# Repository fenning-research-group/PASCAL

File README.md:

# Perovskite Automated Spin Coat Assembly Line (PASCAL)

## Motivation

PASCAL is an automated platform for spin coating and annealing thin films onto small (>2x2 cm) substrates, aimed af increasing experimental throughput in the pursuit of designing better perovskite solar cells. Perovskite solar cells are infinitely tunable, as they can be formed with combinations of nearly half of the periodic table, presenting the excitement of limitless possibilities and the curse of dimensionality. With PASCAL, we aim to increase our experimental search rate by orders of magnitude, enabling a more systematic and exhaustive approach toward exploring the vast compositional space of interest for solar cell design.

## Hardware

### CAD schematics of PASCAL

### Liquid handler preparing precursor solution mixtures for a compositional search

### Liquid handler + spincoater working in conjunction to deposit solution onto substrate.

### Automated Full Sample Fabrication + Characterization Timelapse

https://github.com/fenning-research-group/PASCAL/assets/49666626/01028334-c0f0-4b86-ad78-245d9399b324

## Experimental Planning

- Computed material properties -> manifold embedding / dimensionality reduction into "behavior space"

### Hardware Scheduling

## Active Learning

### intra-run (narrow scope)

- bayesian approach to evaluating sample space

- update compositions of interest using in-line during experiment

### inter-run (wide scope)

- bayesian approach with operator input (XRD, UV-Vis, etc)
- find covariances between composition/fabrication conditions
- point towards broader design philosophies in perovskite solar cells

## In-Line Characterization

- Widefield PL camera

- RGB Imaging for color determination

## Dependency
  - python=3.7.9=h26836e1_0

## Addons 

See our [fenningresearchgroup.com/https://github.com/fenning-research-group/PASCAL_TrainView
](https://github.com/fenning-research-group/PASCAL_TrainView)https://github.com/fenning-research-group/PASCAL_TrainView

and https://github.com/dnzckn/BO-PV repo's for additional capabilities

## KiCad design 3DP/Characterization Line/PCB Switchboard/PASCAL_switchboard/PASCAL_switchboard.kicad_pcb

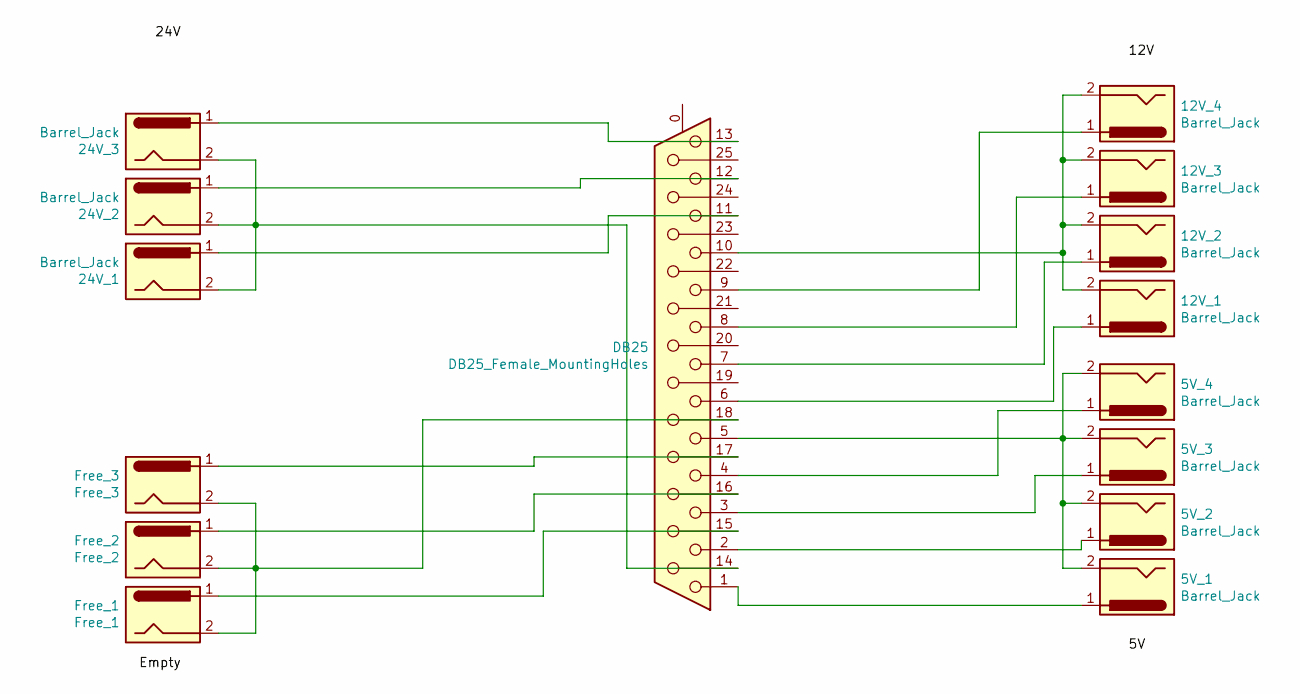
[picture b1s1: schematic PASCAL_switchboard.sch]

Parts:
5V_1, 5V_2, 5V_3, 5V_4, 12V_1, 12V_2, 12V_3, 12V_4, 24V_1, 24V_2, 24V_3: Barrel_Jack; BarrelJack_CUI_PJ-063AH_Horizontal
DB25: DB25_Female_MountingHoles; DSUB-25_Male_Horizontal_P2.77x2.84mm_EdgePinOffset7.70mm_Ho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
Free_1: Free_1; BarrelJack_CUI_PJ-063AH_Horizontal
Free_2: Free_2; BarrelJack_CUI_PJ-063AH_Horizontal
Free_3: Free_3; BarrelJack_CUI_PJ-063AH_Horizontal

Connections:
unnamed: 5V_1.1, DB25.1
unnamed: 5V_1.2, 5V_2.2, 5V_3.2, 5V_4.2, DB25.5
unnamed: 5V_2.1, DB25.2
unnamed: 5V_3.1, DB25.3
unnamed: 5V_4.1, DB25.4
unnamed: 12V_1.1, DB25.6
unnamed: 12V_1.2, 12V_2.2, 12V_3.2, 12V_4.2, DB25.10
unnamed: 12V_2.1, DB25.7
unnamed: 12V_3.1, DB25.8
unnamed: 12V_4.1, DB25.9
unnamed: 24V_1.1, DB25.11
unnamed: 24V_1.2, 24V_2.2, 24V_3.2, DB25.14
unnamed: 24V_2.1, DB25.12
unnamed: 24V_3.1, DB25.13
unnamed: DB25.15, Free_1.1
unnamed: DB25.16, Free_2.1
unnamed: DB25.17, Free_3.1
unnamed: DB25.18, Free_1.2, Free_2.2, Free_3.2

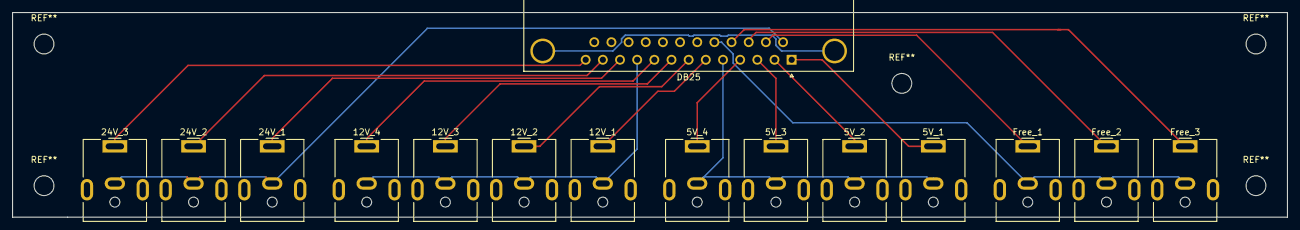
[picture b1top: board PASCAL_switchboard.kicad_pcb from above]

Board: 2 copper layers, 205.7 x 33.0 mm, 15 parts (0 on the bottom side), 18 nets.

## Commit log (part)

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2023-02-05 add load_all_generator to lazy load data
2023-02-15 working for hotplate scheduling
2023-02-17 update positions and calibrations
2023-03-10 added 3d printed parts for safe keeping
2023-03-15 new cals
2023-04-11 tray
2023-04-26 thank you for your patience - ken
2023-04-27 update cals
2023-05-04 cals
2023-07-12 Update OT2Listener_1000left300right.py
    addressing leaking pipette during pre_mixing
2023-07-12 speed adjustment not correct
2023-07-12 allow volume argument to air_gap
2023-07-12 fixed import bug
2023-07-26 parts
2023-08-17 17mm calibration updates
2023-09-15 calc
2023-10-07 st1_calibrations
2023-10-13 change
2023-11-13 updatecal
2023-12-05 updatecals
2024-02-10 dataset
2024-02-10 data
2024-03-13 rename
2024-04-07 demo video
2024-04-07 cad files
2024-04-12 new gripper cals
2024-04-23 drop out relay, update readme
2024-04-30 stashing cal files
2024-05-13 change filename
2024-06-18 tray cals
2024-09-04 new
    new
2024-09-09 new cals
    new
2024-09-26 Updated Calibrations...this is a good one :) -JP
2024-10-14 Adding additional installation instructions (still need to add for Mac)
2024-10-14 Update setup.py to include "doepy" package
2024-10-15 PASCAL speed up! Removed unnecessary G-code command (M400) that was used much more frequently than necessary. Still being run right before gripper commands are executed. Need to verify CL axis still 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
2024-10-22 commiting changes that are close but not quite working yet for calibration fixes
2024-10-25 added in changes to gantry movement that weren't pushed earlier
2024-11-08 added code to reset runs history and boot scripts after every run to make opentrons more reliable. also removed need to get ip for m.run()
2024-11-08 updated speeds in workers.py so that timings can be set more accurately between moves in a run. still some work to do to optimize movements
2024-11-18 rtwe
    twr5
2024-11-22 made some changes to help improve opening, 1in samples is max for this wing size
2024-12-18 minor changes
2024-12-18 updated limits to allow for correct calibration
2024-12-18 made changes to how OT2 python file is generated, need to use this new code for opentrons to work!
2025-01-02 adding new branch to make .calibrate() load from calibration.yaml instead of constants
2025-01-02 fixed small bug with get_p0
2025-01-02 made changes to calibration, but not reading calibration file correctly upon running .calibrate()
2025-01-02 saving changes for commit
2025-01-03 fixed default openwidth, temp fix
2025-01-06 characterization line updates
2025-01-14 commenting out lines for characterization line
2025-01-14 increased opening width of gripper slightly
2025-01-14 removing code to for cl axis
2025-01-16 some more things that may or may not have been necessary to remove for optional char
2025-01-18 added ability for char to be optional, won't break if not connected (untested)
2025-01-18 calibration changes
2025-01-18 Update maestro.py
    Fixed typo in characterization
2025-01-24 made changes to accomodate new gripper design with larger servo
2025-01-24 comments for Nic
2025-01-31 added code that will skip spectrometer if characterization line is needed, but other characterizations are still needed
2025-02-03 added uid to output log JSON
2025-02-03 made changes to hopefully make USB connections more reliable
2025-02-11 added small documentation to barcode code
2025-02-14 fixed issues with odrive that may have been caused by incorrectly set PID params
2025-02-14 found correct pwm for 25mm
2025-02-14 added yaml files for new sample tray and hotplate
2025-02-15 additional software changes required for opening at both 27mm and 12mm (2mm more than sample width)
2025-03-25 Update maestro.pyh
    fhf
2025-03-27 chuck lock and a few calibration changes
2025-06-05 PASCAL Revival Edits
    Made changes to make PASCAL operational. Fixed spincoater tuning process, liquidhandler communication process. -Eric
2025-06-09 gantry motion print statements
2025-06-10 gantry printing
2025-06-10 testing gripper change
2025-06-10 ported new usb connection method to 2023 branch for testing of old working version
2025-06-11 workspace frame transition fixes
    attempt 1 of repairing gantry transition across OT2/non-OT2 target_frames.
2025-06-11 more gantry edits to return to original pascal behavior
2025-06-12 pascal gantry edits -Eric
2025-06-12 more gantry quick print statements -Eric
2025-06-13 mild print statement edits for troubleshooting -Eric
2025-06-13 gripper timouts
2025-06-19 Updated for new computer setup
2025-06-20 calibrations -Eric
2025-06-25 Update liquidlabware content plotting for readability
2025-06-26 corrections to liquidlabware markers
2025-06-26 Variation of June2025-fixes for 25.3mm sample functionality
2025-07-23 Transmission, cl.axis bug fixes
2025-07-31 cl.axis._getposition() typo fix
2025-07-31 Formal semi-manual PASCAL branch.
    Eliminates the need to rely on the Gantry/Gripper in any amount to use PASCAL for sample fabrication/characterization. With this branch, it is possible to make limitless samples per batch, only limit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
2025-07-31 edits for input file generation
2025-07-31 fix to bug that breaks m.stop() when only doing characterization without any opentrons communication.
2025-08-22 opentrons stop shaking
    decreases the speed of opentrons pipette arm x-y motions, plus some fixes for the humanoperator functionality.
2025-08-22 quality of life updates
    easier pascalplanner to switch between gantry/humanoperator
2025-09-04 Gantry stop crashing, PASCALPlanner cross-compatibility fix
    PASCALPlanner failed to work on MacOS due to requiring the wmi package within frgpascal/hardware/helpers.py Not necessary if only going to write the input files without actually running PASCAL. Gantr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
2025-09-18 Easy Read Sample Tray Plots
    Updated how sampletray plots are generated within PASCALPlanner() to make it easier to decipher the legends of each traymaps.
2025-10-14 characterization axis revival, realignments
2025-11-16 Spincoater, Opentrons, Gantry updates
    Added functionality for using the lights on opentrons during a run, for updating/replacing the gantry control board firmware, and for including/bypassing the Worker_SpincoaterLiquidHandler() in case 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
2025-11-18 spincoater dummy error fix
    slight typo in the "skip spincoater" logic that caused a meaningless error statement to print in the command prompt during bootup.
2025-11-18 Create CAD files
2025-12-10 opentrons, transmission fixes
2026-02-12 attempt at making ot2 protocol generation generate without ntp dependency so it can work without internet connection
2026-02-23 redefined connect procedure to use COM Ports on laptop
2026-02-23 Added Functionality for single sample opentrons spincoat
2026-02-24 updates for better manual spincoats
2026-02-24 added compatibility with either serial or socket connection for control of Gantry.
2026-02-24 fixed Gantry()._waitformovement() logic
    changes line 525 to control when to start communicating with the output position response of the gantry as it moves, depending on whether the gantry's control is through serial or socket connections.
2026-02-24 fix echo command for RepRap settings
2026-02-25 gantry is alive
2026-02-25 fakeout edits to run on external laptop
2026-02-25 fake spincoater timing worker
2026-02-25 fake odrive._libfibre flushing protocol updates.
2026-02-27 Opentrons environment update
2026-02-28 Geometry definitions
2026-02-28 legacy serial communications for gantry
2026-02-28 moved transition nudge distance into hardwareconstants
2026-03-01 minor syntax fixes
2026-03-02 abstractions of the communicator classes
2026-03-03 ready-to-test implementation of NewGantry
    Definition of base communication and motion control classes, usage of base classes to define particular subtypes of g-code communication, motion controllers, implementation of user choice at runtime 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
2026-03-04 spincoater and hotplate documentation updates
2026-03-04 load edits
2026-03-04 edits
2026-03-04 forgot gohome in BaseMotionControl
2026-03-05 communication issues
2026-03-05 motion updates
2026-03-09 geometry/spincoater docs
2026-03-11 edits to gantry for troubleshooting motion
    These should be next migrated onto the NewGantry parent class methods for future deployment.
2026-03-13 calibration changes to ensure the pitch of a tray is true.
2026-03-17 calibrations, ip issues.
2026-03-27 edits to gantry calibrations
2026-03-27 options for new sampletray interpolations
2026-03-27 NewGantry bugs
2026-03-27 trying out RBFInterpolator for sample tray coordinates now.
2026-03-27 SampleTray calibrations, RBFInterpolator for xy, LinearNDInterpolator for z
2026-03-30 updated logic for sample place onto a sampletray
    Now GantryGripper will move to the destination slot on a sample tray, attempt to release the sample, then move slightly upwards ~0.1-0.15mm and open gripper 5% more to loose the gripper in case it st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
2026-04-06 fix for roboflow 2026 compatibility
2026-04-09 removing legacy retry decorator wrapping from gantry.
2026-04-10 explicit ODrive enumerations
2026-04-14 gantry installed!
2026-04-21 updated firmware on cl.axis control board. Gantry documentation edits.
2026-04-24 changed duet board connections to eliminate crash failure mode
    Was possible for a user to close the PASCAL prompt but leave the Duet board powered on, and then restart the PASCAL prompt, without actually flushing any in-progress motion commands from the Duet boa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
2026-04-24 minor edits
2026-04-24 tab typo in Duet3Mini5Plus_MotionControl().update()
2026-04-24 BaseMotionControl position setter edits.
2026-04-24 minor edits to socket connection, base gantry update
2026-04-24 _movecommand(), moveto() debug print statements
2026-04-24 fixed BaseMotionControl()._movecommand() conditional
    Previously the conditional list to check if all positions were equivalent erroneously checked for if at least one x, y, z coordinate of target and position were same, causing any motion of less than 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
2026-04-24 NewGantry moving almost
2026-04-27 SocketCommunicator send_gcode minor tweak
2026-04-27 Duet motion control update() method logic revision
2026-04-28 initial commit
    This branch is for development of dynamic changing of the sample size and any associated logic/settings within PASCAL, so that switching modalities can exist within a singular branch long-term.
2026-04-28 new workspace version syntax for multi sample size
2026-05-01 probably working multi sample size
2026-05-01 behave
2026-05-01 tray calibrations, spincoater operation tests
2026-05-05 revised Tray1 Tray2 wrappers for experimental design
2026-05-05 PASCAL runs!
2026-05-07 camera image capture (untested)
2026-05-07 unstick from hotplate!
2026-05-12 proper image saving
2026-05-12 minor edits to place on spincoater chuck better
2026-05-12 quick fix
2026-05-14 image capture timing fix + (maybe) ml model
2026-05-26 codified smooth opentrons motions, re-calibrated cl.axis positions
2026-05-27 Added opentrons app print statements during a run
2026-05-27 attempt to have opentrons app notify the begin of spincoat
2026-05-28 new workers logger
2026-05-28 Added loggers for all workers
2026-05-29 edits to standalone spincoat mode
2026-05-29 can we slow down the touch_tip?
2026-05-30 editing functionality of spincoat for standalone mode
2026-05-30 calibrations, bug squashing
2026-06-08 Changed OT-2 tip pick place to try and stop shakes.
2026-06-08 slow tip grab working
2026-06-11 finished v1 of per-sample OT2 Motion setting updates
2026-06-11 minor typos in dynamic OT2 settings mode
2026-06-12 typo corrections
2026-06-12 customized touch_tip to move more smoothly now
2026-06-16 variable touch_tip custom motion speeds works!
2026-06-16 tried to log all OT2 action durations during runtime
2026-06-17 attempt at saving the liquid handler action timing metadata during run
2026-06-17 also save the associated unique identifiers of the OT-2 droptime tasks, for metadata tracking.
2026-06-25 updated motion logs in OT-2 operation
2026-06-25 minor edits to OT-2 motion time logging
